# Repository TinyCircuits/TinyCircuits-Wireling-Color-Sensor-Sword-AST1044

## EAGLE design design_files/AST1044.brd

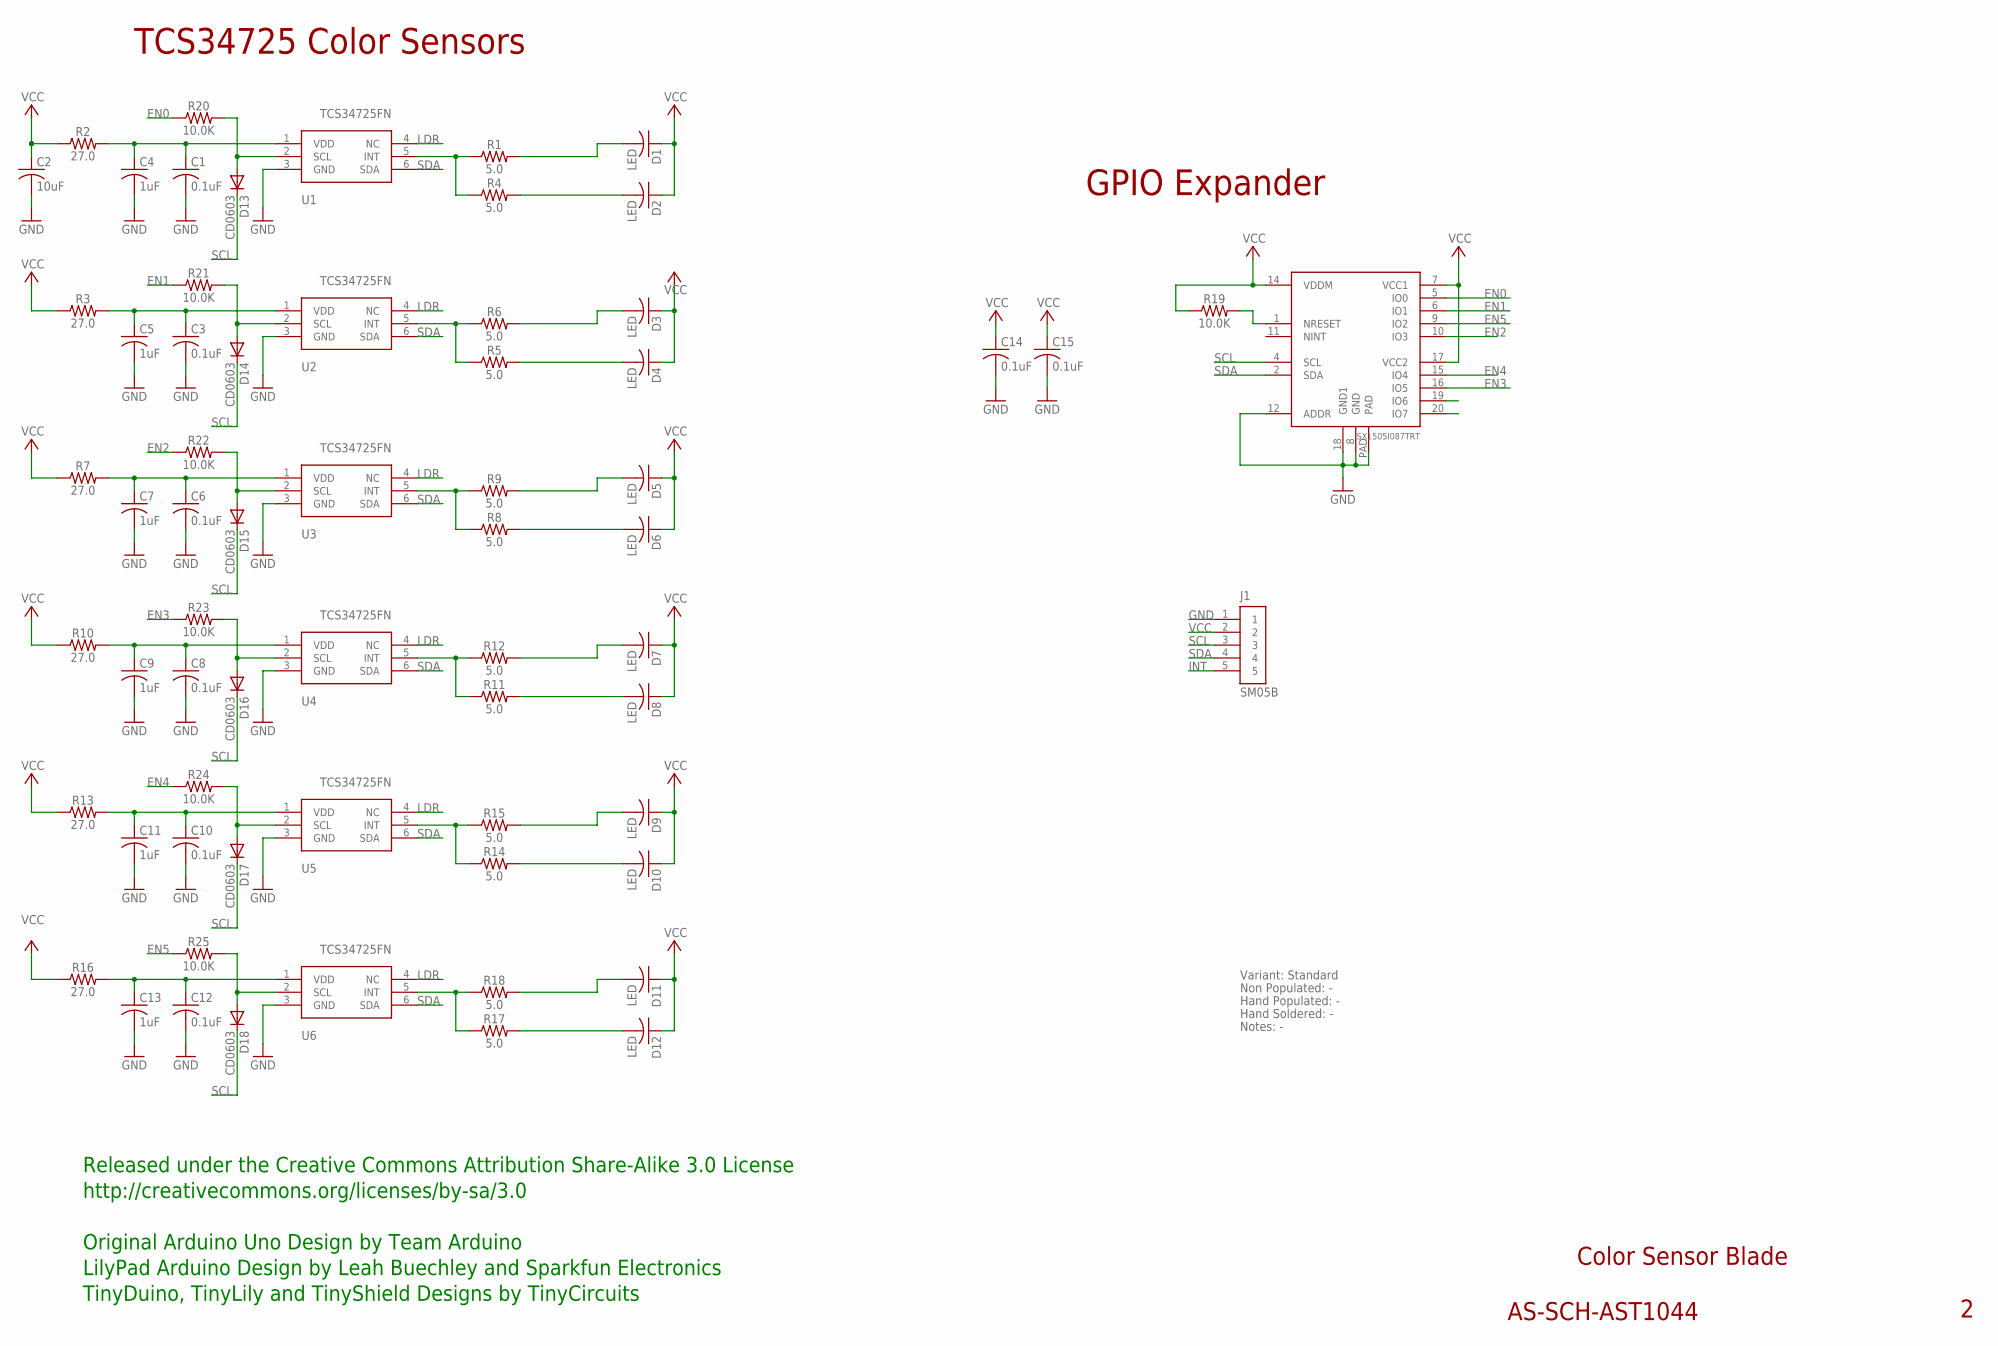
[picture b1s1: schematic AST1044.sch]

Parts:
C1, C3, C6, C8, C10, C12, C14, C15: 0.1uF; C0402
C2: 10uF; C0603
C4, C5, C7, C9, C11, C13: 1uF; C0402; PARTNO AS-ITM-00105
D1, D2, D3, D4, D5, D6, D7, D8, D9, D10, D11, D12: LED; C1206; PARTNO AS-ITM-00049
D13, D14, D15, D16, D17, D18: CD0603; 0603
J1: SM05B; JST_SH_5X1_EDGE
R1, R4, R5, R6, R8, R9, R11, R12, R14, R15, R17, R18: 5.0; 0402; PARTNO AS-ITM-00289
R2, R3, R7, R10, R13, R16: 27.0; 0402
R19, R20, R21, R22, R23, R24, R25: 10.0K; 0402
U1, U2, U3, U4, U5, U6: TCS34725FN; TSL2572; PARTNO AS-ITM-00140
U7: SX1505I087TRT; QFN-UT20

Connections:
EN0: R20.1, U7.5 (IO0)
EN1: R21.1, U7.6 (IO1)
EN2: R22.1, U7.10 (IO3)
EN3: R23.1, U7.16 (IO5)
EN4: R24.1, U7.15 (IO4)
EN5: R25.1, U7.9 (IO2)
GND: C1.2, C2.2, C3.2, C4.2, C5.2, C6.2, C7.2, C8.2, C9.2, C10.2, C11.2, C12.2, C13.2, C14.2, C15.2, J1.1, U1.3 (GND), U2.3 (GND), U3.3 (GND), U4.3 (GND), U5.3 (GND), U6.3 (GND), U7.8 (GND), U7.12 (ADDR), U7.18 (GND1), U7.PAD
INT: J1.5
LDR: U1.4 (NC), U2.4 (NC), U3.4 (NC), U4.4 (NC), U5.4 (NC), U6.4 (NC)
unnamed: R1.1, R4.1, U1.5 (INT)
unnamed: C1.1, C4.1, R2.2, U1.1 (VDD)
unnamed: D2.2, R4.2
unnamed: D1.2, R1.2
unnamed: C3.1, C5.1, R3.2, U2.1 (VDD)
unnamed: R5.1, R6.1, U2.5 (INT)
unnamed: D4.2, R5.2
unnamed: D3.2, R6.2
unnamed: C6.1, C7.1, R7.2, U3.1 (VDD)
unnamed: R8.1, R9.1, U3.5 (INT)
unnamed: D6.2, R8.2
unnamed: D5.2, R9.2
unnamed: C8.1, C9.1, R10.2, U4.1 (VDD)
unnamed: R11.1, R12.1, U4.5 (INT)
unnamed: D8.2, R11.2
unnamed: D7.2, R12.2
unnamed: C10.1, C11.1, R13.2, U5.1 (VDD)
unnamed: R14.1, R15.1, U5.5 (INT)
unnamed: D10.2, R14.2
unnamed: D9.2, R15.2
unnamed: C12.1, C13.1, R16.2, U6.1 (VDD)
unnamed: R17.1, R18.1, U6.5 (INT)
unnamed: D12.2, R17.2
unnamed: D11.2, R18.2
unnamed: D13.A, R20.2, U1.2 (SCL)
unnamed: D14.A, R21.2, U2.2 (SCL)
unnamed: D15.A, R22.2, U3.2 (SCL)
unnamed: D16.A, R23.2, U4.2 (SCL)
unnamed: R19.2, U7.1 (NRESET)
unnamed: D17.A, R24.2, U5.2 (SCL)
unnamed: D18.A, R25.2, U6.2 (SCL)
SCL: D13.C, D14.C, D15.C, D16.C, D17.C, D18.C, J1.3, U7.4 (SCL)
SDA: J1.4, U1.6 (SDA), U2.6 (SDA), U3.6 (SDA), U4.6 (SDA), U5.6 (SDA), U6.6 (SDA), U7.2 (SDA)
VCC: C2.1, C14.1, C15.1, D1.1, D2.1, D3.1, D4.1, D5.1, D6.1, D7.1, D8.1, D9.1, D10.1, D11.1, D12.1, J1.2, R2.1, R3.1, R7.1, R10.1, R13.1, R16.1, R19.1, U7.7 (VCC1), U7.14 (VDDM), U7.17 (VCC2)

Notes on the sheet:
Color Sensor Blade
AS-SCH-AST1044
TCS34725 Color Sensors
Released under the Creative Commons Attribution Share-Alike 3.0 License
http://creativecommons.org/licenses/by-sa/3.0
Original Arduino Uno Design by Team Arduino
TinyDuino, TinyLily and TinyShield Designs by TinyCircuits
LilyPad Arduino Design by Leah Buechley and Sparkfun Electronics
Variant: Standard
Non Populated: -
Hand Populated: -
Hand Soldered: -
Notes: -
GPIO Expander

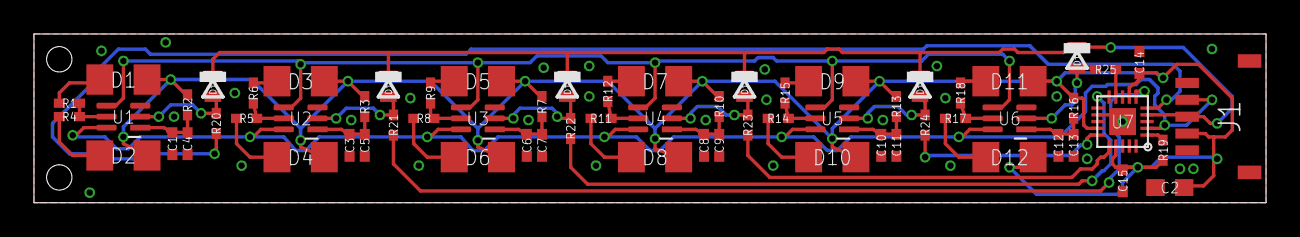
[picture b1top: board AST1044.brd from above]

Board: 2 copper layers, 73.0 x 10.0 mm, 67 parts (0 on the bottom side), 42 nets.

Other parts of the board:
U$1: DOCFIELD-TINYCIRCUITS-PCB

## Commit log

2019-12-17 updated documentation
